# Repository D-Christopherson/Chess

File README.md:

This repo contains all the relevant files for a chess board I'm building.

The top level directory contains a chess engine I wrote in Kotlin, serve with Spring Boot, and deploy to AWS with Terraform.
I'd written a chess engine in Java using two-dimensional arrays to represent the board early on in college, so I wanted 
to try bitboards this time. The goal is to represent the board as a set of 64-bit numbers since operations with those should 
be much faster than an array. 

Some hand wavy math for moving a rook up one square:
* One clock cycle to multiply the first index by the width of the outer array
* One clock cycle to add that to the base address of the array
* One clock cycle to multiply the second index by the data type the inner array contains
* One clock cycle to add that to the address calculated in step 2
* One clock cycle to null out that square
* Repeat above for the target square

With bitboards (ideally)
* One clock cycle to left shift the number representing the rook by 8

`chess_electronics` contains the schematic and PCB design for the circuit board that connects the microcontroller, RFID 
reader, and antennas together. These were created in KiCad.

`microcontroller` contains the code running on the ESP32. The microcontroller is responsible for controlling the 8 separate
8 way switches, driving the RFID reader over UART, and converting the RFID tags into pieces to create the actual game state.

`mobile_app` contains a proof of concept android app that reads the board state from the microcontroller over bluetooth 
and sends that state to the chess engine in AWS over the internet. The ESP32 could do this itself since it has Wi-Fi capabilities,
but it'd be a huge pain to reprogram the Wi-Fi credentials if I want to take the board to a club.

Here's an MS Paint breakdown of the board itself.

Eventually I'd like to strap an electromagnet to a pair of linear slides under the board to have the board play against 
a human. This product already exists, but costs between \$500 and \$1100.
The bill of materials for this build so far is:
* ESP32 dev board - $16 for a 3 pack on Amazon
* 8x SN74LV4051AN 8 way switch - $5.52 for 10 on DigiKey (cheaper than buying 8)
* 64x 13.56MHz RF antennas - $32 on DigiKey
* 65x 10nF ceramic capacitor - I bought a variety pack and used 47 nF capacitors after running out of 10nF. These will cost 
\$5-$30 on DigiKey. They just need to be capacitors that don't have polarity and are large enough to not add a ton of impedance 
(10nF is plenty).
* 8x 16 position screw terminals - $16 on DigiKey. I bought these not realizing that they're just 2 and 3 position terminals
connected to each other with a little plastic slide. Buying 64x 2 position terminals might be cheaper.
* DLP RFID2 - $37.95 on DigiKey. I've read that this chip is pretty outdated and has some firmware bugs. There might be 
something cheaper nowadays. The key is just to make sure it's compatible with the same frequency as the tags/antennas used 
and also has a pin for an external antenna.
* 5x circuit boards (as that's the minimum quantity most factories will make) - ~\$120. I also have a directory in `chess_electronics` 
called `Modular_Antenna` which crams the screw terminals and capacitors into a small board independent of one that would 
house the microcontroller and RFID reader (I have not designed this motherboard yet). This should bring the cost down to 
$30 or so since there's less wasted space. I'm just not sure if it's acceptable to run signal lines so close to other traces.

For the LCD screen you'll also need:
* 1x LCD screen - I'm using an LCD1602 module. It looks like these run \$5-\$10 depending on the source.
* 8x normally closed (Form B) relays. I quickly ran out of GPIO pins wiring each INH pin of the multiplexers to the
microcontroller directly, so these are going to connect the power plane to the INH pin. I'll have a 9th multiplexer that
connects to each of the relays. This brings the pins used for the multiplexers down to 6 from 11.
* 2x additional multiplexers. One for the multiplexer that now controls the INH pins and one for the LCD screen module.
The LCD screen has 8 data pins which the multiplexer will control as well as three pins for controlling the data on screen
and one pin for contrast.

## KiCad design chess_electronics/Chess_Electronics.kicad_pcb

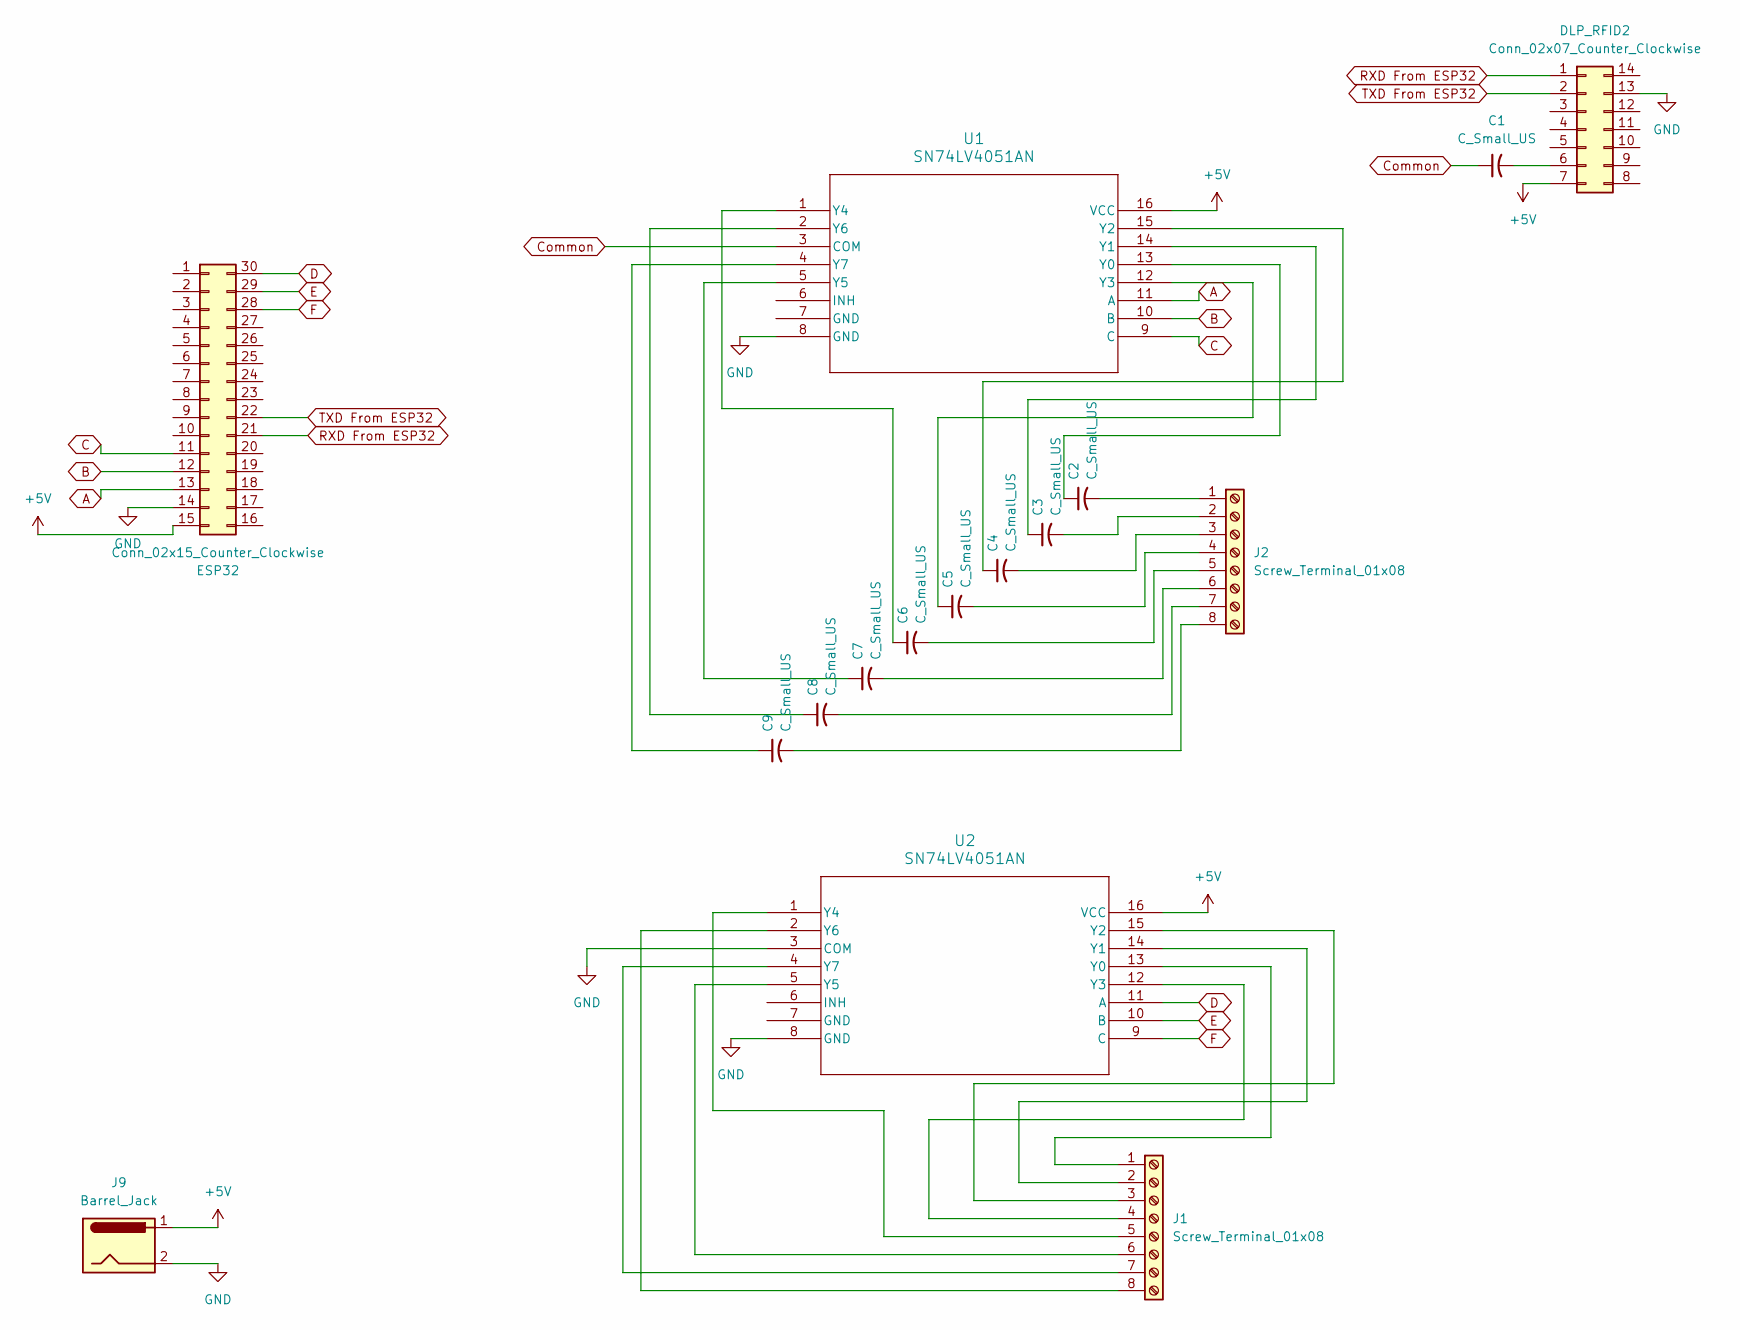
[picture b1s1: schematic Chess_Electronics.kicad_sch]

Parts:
C1, C2, C3, C4, C5, C6, C7, C8, C9: C_Small_US; C_Axial_L3.8mm_D2.6mm_P7.50mm_Horizontal
DLP_RFID2: Conn_02x07_Counter_Clockwise; PinHeader_2x07_P2.54mm_Vertical
ESP32: Conn_02x15_Counter_Clockwise; PinHeader_2x15_P2.54mm_Vertical
J1, J2: Screw_Terminal_01x08; TerminalBlock_MaiXu_MX126-5.0-08P_1x08_P5.00mm
J9: Barrel_Jack; CUI_PJ-037A
U1, U2: SN74LV4051AN; N16

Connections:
+5V: DLP_RFID2.7, ESP32.15, J9.1, U1.16 (VCC), U2.16 (VCC)
A: ESP32.13, U1.11 (A)
B: ESP32.12, U1.10 (B)
C: ESP32.11, U1.9 (C)
Common: C1.1, U1.3 (COM)
D: ESP32.30, U2.11 (A)
E: ESP32.29, U2.10 (B)
F: ESP32.28, U2.9 (C)
GND: DLP_RFID2.13, ESP32.14, J9.2, U1.8 (GND), U2.3 (COM), U2.8 (GND)
unnamed: C1.2, DLP_RFID2.6
unnamed: J1.1, U2.13 (Y0)
unnamed: J1.2, U2.14 (Y1)
unnamed: J1.3, U2.15 (Y2)
unnamed: J1.4, U2.12 (Y3)
unnamed: J1.5, U2.1 (Y4)
unnamed: J1.6, U2.5 (Y5)
unnamed: J1.7, U2.4 (Y7)
unnamed: J1.8, U2.2 (Y6)
unnamed: C2.2, J2.1
unnamed: C3.2, J2.2
unnamed: C4.2, J2.3
unnamed: C5.2, J2.4
unnamed: C6.2, J2.5
unnamed: C7.2, J2.6
unnamed: C8.2, J2.7
unnamed: C9.2, J2.8
unnamed: C2.1, U1.13 (Y0)
unnamed: C3.1, U1.14 (Y1)
unnamed: C4.1, U1.15 (Y2)
unnamed: C5.1, U1.12 (Y3)
unnamed: C6.1, U1.1 (Y4)
unnamed: C7.1, U1.5 (Y5)
unnamed: C8.1, U1.2 (Y6)
unnamed: C9.1, U1.4 (Y7)
RXD From ESP32: DLP_RFID2.1, ESP32.21
TXD From ESP32: DLP_RFID2.2, ESP32.22

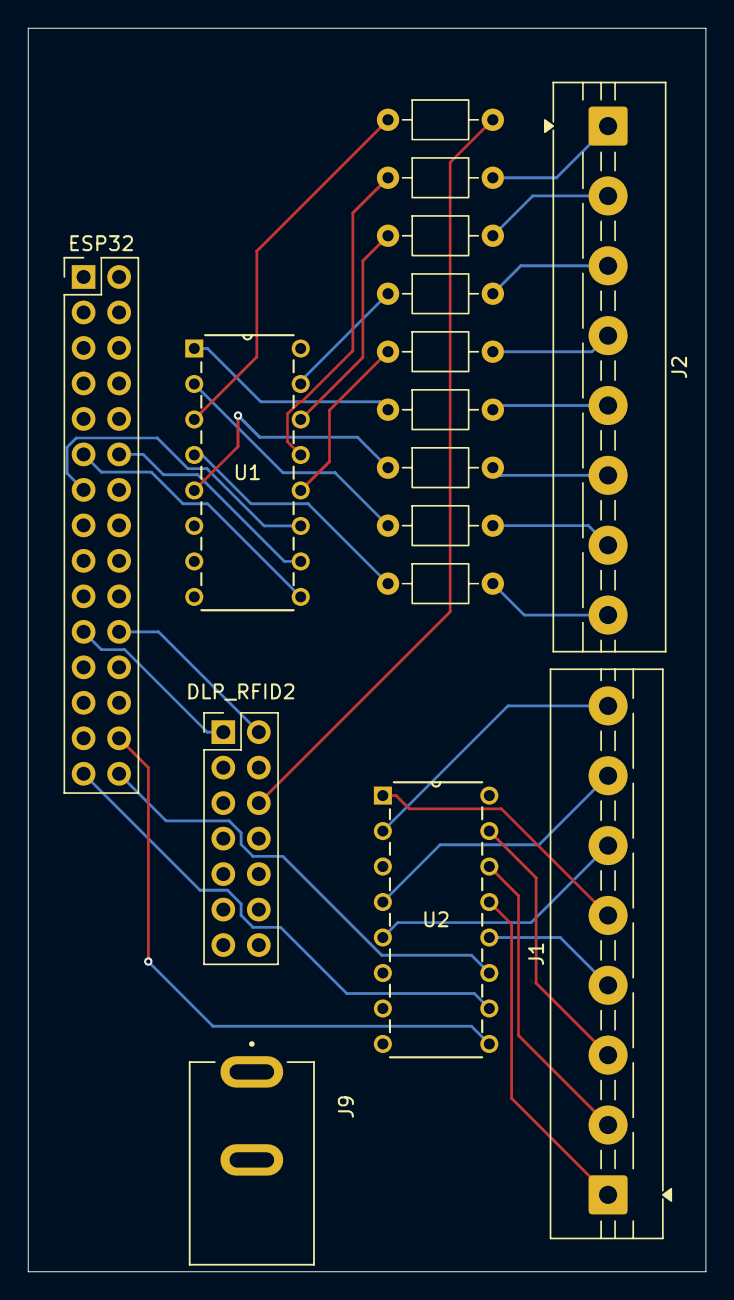
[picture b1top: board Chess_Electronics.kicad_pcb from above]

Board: 4 copper layers, 48.5 x 89.0 mm, 16 parts (0 on the bottom side), 36 nets.

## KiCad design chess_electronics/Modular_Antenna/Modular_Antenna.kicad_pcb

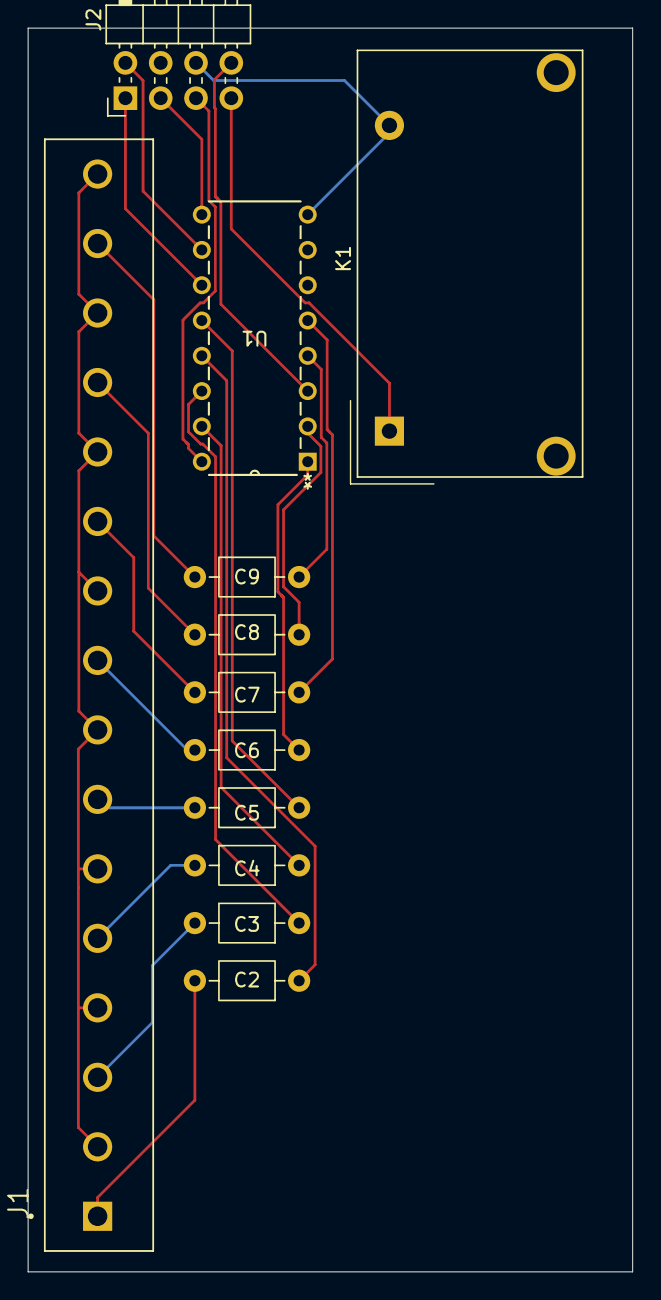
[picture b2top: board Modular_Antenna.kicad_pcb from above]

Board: 2 copper layers, 43.5 x 89.5 mm, 12 parts (0 on the bottom side), 24 nets.

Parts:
C2, C3, C4, C5, C6, C7, C8, C9: C_Small_US; C_Axial_L3.8mm_D2.6mm_P7.50mm_Horizontal
J1: Screw_Terminal_01x16; CUI_TB003-500-P16BE
J2: Conn_02x04_Counter_Clockwise; PinHeader_2x04_P2.54mm_Horizontal
K1: Relay_SPST-NC; Relay_SPST_Zettler-AZSR131
U1: SN74LV4051AN; N16

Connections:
GND: J1.2, J1.4, J1.6, J1.8, J1.10, J1.12, J1.14, J1.16
unnamed: C2.2, J1.1
unnamed: C3.2, J1.3
unnamed: C4.2, J1.5
unnamed: C5.2, J1.7
unnamed: C6.2, J1.9
unnamed: C7.2, J1.11
unnamed: C8.2, J1.13
unnamed: C9.2, J1.15
unnamed: J2.1, U1.11 (A)
unnamed: J2.2, U1.10 (B)
unnamed: J2.3, U1.9 (C)
unnamed: J2.5, U1.16 (VCC)
unnamed: J2.6, K1.A2, U1.8 (GND)
unnamed: J2.7, K1.A1
unnamed: J2.8, U1.3 (COM)
unnamed: C2.1, U1.13 (Y0)
unnamed: C3.1, U1.14 (Y1)
unnamed: C4.1, U1.15 (Y2)
unnamed: C5.1, U1.12 (Y3)
unnamed: C6.1, U1.1 (Y4)
unnamed: C7.1, U1.5 (Y5)
unnamed: C8.1, U1.2 (Y6)
unnamed: C9.1, U1.4 (Y7)

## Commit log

2025-05-22 Initial commit of build configuration
2025-05-22 Initial commit of engine, no castling and limited tests
2025-05-22 Remove unnecessary array copies and list iteration from move generation for a 5% performance increase
2025-05-23 Minor readability improvement in minimax and added comments for less obvious actions
2025-05-23 Update gradle to resolve an error when trying to add vm arguments to tests
2025-05-26 Fix alpha-beta pruning comparison leading to an extra 2 ply search in the same amount of time, avoid searching through the transposition table's best move twice
2025-05-26 Add en-passant FEN parsing and move generation
2025-06-03 Correct transposition entry cutoff comparison
2025-06-03 Shore up move generation unit tests in preparation for refactoring
2025-06-03 Significantly reduce duplicated code for move generation of sliding pieces
2025-06-03 Reduce code duplication for pawn captures
2025-06-12 Downgrade to java 21 in prep for using google's distroless base image
2025-06-12 Dockerize the service
2025-07-14 Add deployment infrastructure
2025-11-22 Remove loop from evaluate API so it only evaluates the existing position. Update terraform to deploy on version change
2025-11-22 Add initial pass of microcontroller code. It currently scans all 64 antennas and reports the FEN to the mobile app over bluetooth
2025-11-22 Add proof of concept for mobile app. It breaks most design rules running everything on the main thread
2025-11-22 Add forgotten tf file for version number
2025-12-05 Remove seemingly unnecessary RF enable/disable commands. It ran fine without them at about 3 times the speed
2025-12-05 Add forgotten gradle configuration for the mobile app
2025-12-09 Add circuitboard schematic and pcb design
2025-12-09 Add readme
2026-01-14 Add normally closed relay to modular antenna design
2026-01-14 Update evaluate API to additionally return evaluation and depth, add simple auth filter
2026-01-14 Refactor out shared code for maximizing and minimizing players
2026-01-14 Stub out tests for BitBoardService, remove duplicate code from move generation
2026-02-09 Update evaluate API to use a regular request body instead of a form
2026-02-09 Add postman collection for evaluate API
2026-04-13 Add inital UI design for board and pieces
2026-04-13 Switch to jetpack compose instead of using a layout
2026-04-13 Fix eval bar width by moving the divider to a subsequent row and offsetting it upward
2026-04-13 Refactor Chessboard into smaller components
2026-04-17 Reverse direction of control so the mobile app drives the microcontroller and add buttons for scanning/eval
2026-04-29 Switch from explicit threads to coroutines. Also move button implementation into each composable by using a function to write state back to the parent
2026-05-16 Update PCB to use two multiplexers by chaining signal and ground in opposite directions
2026-06-24 Add API to route pieces on the gantry. Also upgrade to Spring Boot 4
